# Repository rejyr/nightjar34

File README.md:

# nightjar34

docs WIP

# pcb
## connecting kicad traces
set `File > Board Setup... > Design Rules > Constraints > Copper to edge clearance:` to `0.25` mm

this removes the `The routing start point violates DRC.` error when routing the xiao ble underside pins

# references
- [TOTEM keyboard](https://github.com/GEIGEIGEIST/TOTEM)
- [Architeuthis dux keyboard](https://github.com/tapioki/cephalopoda/tree/main/Architeuthis%20dux)
- [kiai keyboard](https://github.com/makgyber/kiai-split/tree/main)
- [xiao ble resources](https://wiki.seeedstudio.com/XIAO_BLE/#resources)
- [choc v2 switches guide](https://showcase.beekeeb.com/kailh-choc-v2-key-switches/)
- [choc v2 keycaps guide](https://showcase.beekeeb.com/choc-spaced-chocv2-keycaps/)
- [ergogen](https://ergogen.xyz/)
- [FlatFootFox ergogen guide](https://flatfootfox.com/ergogen-introduction/)
- [convert kicad footprints to ergogen](https://nilnil.notion.site/Convert-Kicad-Footprints-to-Ergogen-8340ce87ad554c69af4e3f92bc9a0898)
- [ceoloide ergogen footprints](https://github.com/ceoloide/ergogen-footprints)
- [ergogen v4 footprints](https://github.com/ImStuBTW/ergogen-v4-footprints)
- [CERN OHL v2 license](https://gitlab.com/ohwr/project/cernohl/-/wikis/Documents/CERN-OHL-version-2)
- [nightjar bird](https://en.wikipedia.org/wiki/Nightjar)

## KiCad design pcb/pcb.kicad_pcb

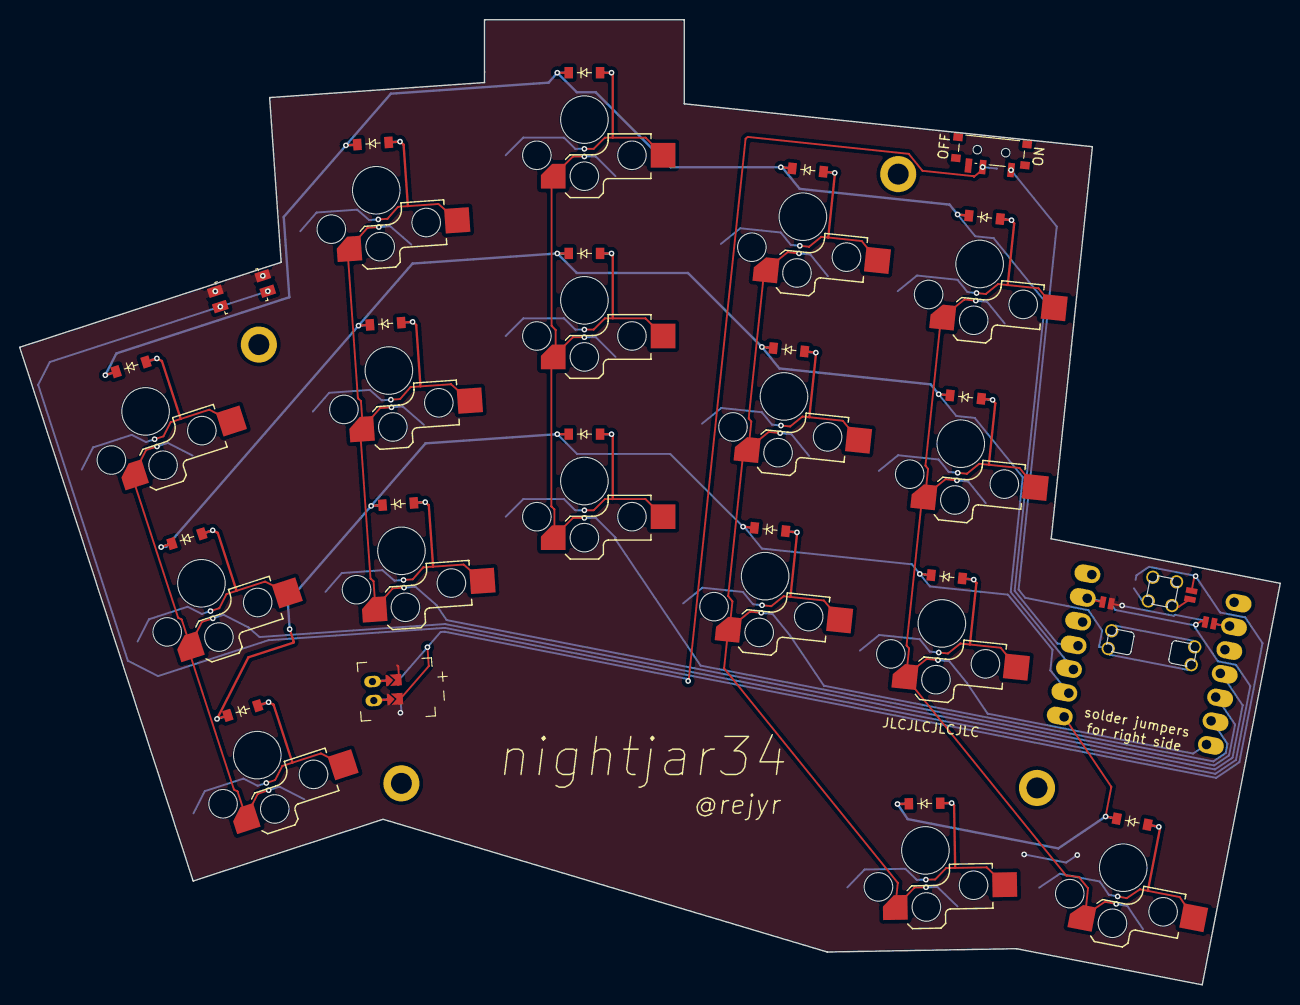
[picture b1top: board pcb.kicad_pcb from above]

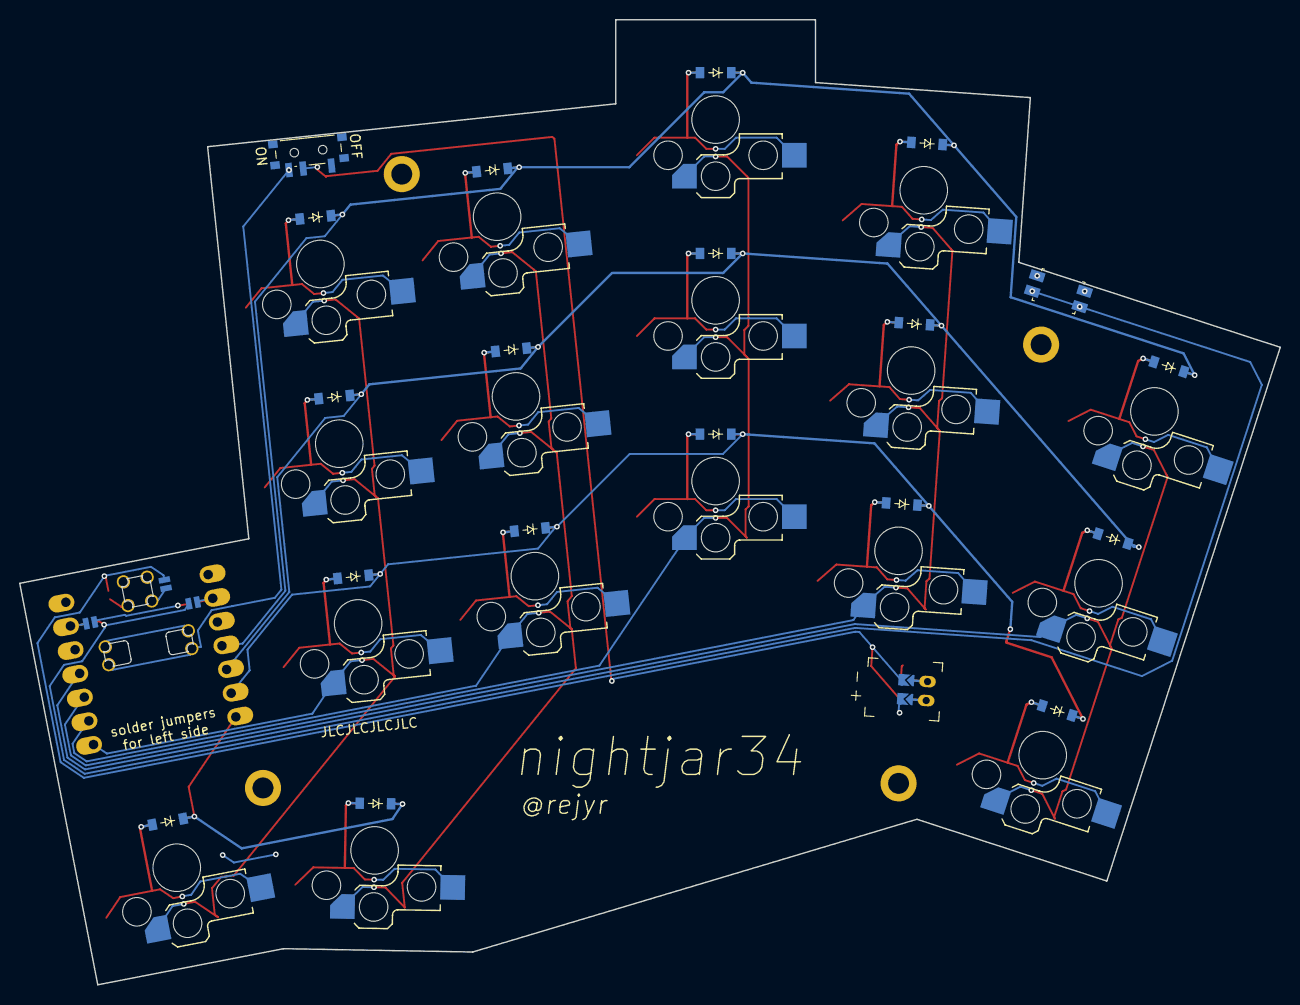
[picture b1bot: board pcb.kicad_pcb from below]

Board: 2 copper layers, 132.5 x 101.5 mm, 46 parts (18 on the bottom side), 33 nets.

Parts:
D1, D2, D3, D4, D5, D6, D7, D8, D9, D10, D11, D12, D13, D14, D15, D16, D17: diode_tht_sod123
H1, H2, H3, H4: mounting_hole_plated
JST1: battery_connector_jst_ph_2
MCU1: mcu_xiao_ble
PWR1: power_switch_smd_side
RST1: reset_switch_smd_side
S1, S2, S3, S4, S5, S6, S7, S8, S9, S10, S11, S12, S13, S14, S15, S16, S17: switch_choc_v1_v2
_1, _2, _3, _4: jumper

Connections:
BAT_P_1: MCU1.19, PWR1.1, PWR1.3
BAT_P_2: JST1.1, PWR1.2
GND: JST1.2, RST1.1, RST1.3, _1.12, _2.22
GND2: MCU1.13, MCU1.18, _2.11, _2.21, _4.11
JST1_1: JST1.11, JST1.21, JST1.31
JST1_2: JST1.12, JST1.22, JST1.32
RST: MCU1.17, RST1.2, RST1.4, _3.11, _3.12, _4.12
c0: MCU1.2, S1.1, S2.1, S3.1, _1.11, _1.21, _1.22, _2.12
c1: MCU1.11, S4.1, S5.1, S6.1
c2: MCU1.10, S7.1, S8.1, S9.1
c3: MCU1.9, S10.1, S11.1, S12.1, S16.1
c4: MCU1.8, S13.1, S14.1, S15.1, S17.1
index_bottom: D10.2, S10.2
index_home: D11.2, S11.2
index_top: D12.2, S12.2
inner_bottom: D13.2, S13.2
inner_home: D14.2, S14.2
inner_top: D15.2, S15.2
layer_cluster: D16.2, S16.2
middle_bottom: D7.2, S7.2
middle_home: D8.2, S8.2
middle_top: D9.2, S9.2
pinky_bottom: D1.2, S1.2
pinky_home: D2.2, S2.2
pinky_top: D3.2, S3.2
r0: D3.1, D6.1, D9.1, D12.1, D15.1, MCU1.4
r1: D2.1, D5.1, D8.1, D11.1, D14.1, MCU1.5
r2: D1.1, D4.1, D7.1, D10.1, D13.1, MCU1.6
r3: D16.1, D17.1, MCU1.7
ring_bottom: D4.2, S4.2
ring_home: D5.2, S5.2
ring_top: D6.2, S6.2
space_cluster: D17.2, S17.2

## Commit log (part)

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2026-06-09 feat: bill of materials
2026-06-09 fix(bom): unescaped pipe in md table
2026-06-09 feat(ergogen): update config.yaml
2026-06-09 feat(ergogen): add row and column nets
    TODO: fix mcu_xiao_ble footprint so reversble pads are not stacked and
    conflicting.
2026-06-09 fix(ergogen): mcu_xiao_ble stacked pads
2026-06-10 fix(ergogen): reversible mcu_xiao_ble cutouts + refactor
2026-06-10 feat(README): kicad traces note
2026-06-10 feat(bom): description column and header tweak
2026-06-10 feat: remove old board outline
2026-06-10 refactor(ergogen): remove unused staggerScale
2026-06-10 feat(ergogen,layout): a dux inspired extra splay and thumb
    changed splays to -14, -4, 0, 6, 6 degrees from middle
2026-06-10 feat(ergogen, layout): +2 pinky stagger, reduce thumb splay
2026-06-10 fix(README): a dux link consistency
2026-06-11 feat(ergogen): place mcu and switches
2026-06-11 refactor(ergogen): remove unnecessary brackets and comments
2026-06-11 feat(ergogen): add jlc utility text
2026-06-11 feat(ergogen): place battery connector
2026-06-11 feat(ergogen): jumper pad footprint
2026-06-11 feat(ergogen): enable_nfc for mcu_xiao_ble footprint
2026-06-11 feat(jumper_pad.js): hardcode pin numbers
2026-06-11 feat(mcu_xiao_ble.js): consistent BAT_P and BAT_N names
2026-06-12 feat(ergogen): power switch pins
2026-06-12 feat(ergogen): flavor silkscreen
2026-06-12 feat(ergogen): mounting holes
2026-06-12 feat(ergogen): ground filled zone
2026-06-12 fix(jumper_pad.js): undefined pad name for single side
2026-06-12 feat(ergogen): rst jumper and jumper instructions
2026-06-12 feat(ergogen): avoid ground zone fill to flippable pads
2026-06-12 feat(ergogen): adjust column pin assignments
2026-06-12 feat(ergogen): BAT_P_{1,2} nets
2026-06-12 feat(pcb): upload pcb
2026-06-12 feat(gerbers): upload gerbers
